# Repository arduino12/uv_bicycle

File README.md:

# UV Bicycle
This repository was created for a rotating laser array above circle colored with [photochromic](https://en.wikipedia.org/wiki/Photochromism) paint.
We were able to draw fading SMS messages on the circle from above by using the ultra violet lasers that activates the photochromatic dye for short periods of time.

The project was done for and in collaboration with the [Bloomfield Science Museum in Jerusalem](http://www.mada.org.il/en) that provided us with the hardware and photochromatic paint.
It was created to serve as a science exhibit that demonstrates the properties of photochromatic dyes.
The code is licensed with the MIT license so you are free to use the code for your own needs.

See the results: https://goo.gl/photos/oJwscTjsn2JnW7Ck9

## Repository Content
[/src/arduino_to_uv/](https://github.com/arduino12/uv_bicycle/tree/master/src/arduino_to_uv) - Arduino code for rotating led/laser array.

[/src/auto_cts/](https://github.com/arduino12/uv_bicycle/tree/master/src/auto_cts) - Arduino code for toggling CTS line to GSM module.

[/src/gsm_to_arduino/](https://github.com/arduino12/uv_bicycle/tree/master/src/gsm_to_arduino) - Pi main code for receiving logging and drawing the SMS messages. 

## Hardware
<img src="https://lh3.googleusercontent.com/Vc9EMIPHA8w_r2cUavsGSQO-o_p-7ncmXYEqYOy1NqUkL5eqGi37OpkXadukhLj22xZ-gRMF1kTlX_NGuJq8BMt3eHUF64rf8kQAkVgELNtqQZ1RMopb4X-rpCWFp0X3qmpbkKMwe0I_WGfFK4Y0_PC1MjWjIJ3T4Ibz2jPdR744nrNS3TW4o-I8bP2ekQa05fymQVjbHknS2VRSZ0DTwl79BUZwA_VtFqYXUJwPtxD64q70xKaM9rZHWuroJr_1Tvtd-X4EULkwvXKUlg1P7ToxBazeEolZ0sMSxTwca8a46mI9U5H4igfo2b5B4D7_b6VAIZAvufg7lnp_SHirEBCOUqLExb3ahMAZRm8fPo9suOPBamb8nU4uetgNMl8iYfZWosMtypwYz0UoY1q7np4bJ6RxMoacF1YhWF4UVPSs5c2owiwA5MacgWr0QcjLhOXokvbC5WcQ38CB4p-cbZNxGNrWULT_6ONU7YTXHPvQaKNxr3c_F1Vqt-jB5_UeZOAFuIAoNEPa4kCFHji4aErF4kzA6CDGKILxqji498P7u0TZostGEw3Fn8uNkkDoxx1JTORTo-OQx-Je5zLs8fBRl57VO6N1IjqmTV3mxX8bAGLKvdmcFl1H1_UraBbP3oRyOuiZWikjajVKhDTIFSlbFYo9egeu3pkob9Kr_HS7YDQ">
<img src="https://lh3.googleusercontent.com/Ws7JQw-yEKeiUe4MuJQAN-q8wx_f5K7RBDDxZ9f8wQQIW_8lA9Yw4n6IqJK_GnT0hbwdW7TLM-m-gelrgOvau5pxB6vvcL0IUWs8IOO5ovuf7cEzAAFZcjh-KP-J3fhh4H8FxVKoyaPNvuyuJGwxkWvGBafbCa8wj3TknDk1y6XuR6KxQ_zH66dlrq7bNpso4gAWbYyNidm6teT94X6_2um_1w_LaygNzx0y9oYFp9pRaNshwGENiCASdAd84XJyoEfFHm6JqLjo-RjeU93c4V7C7xSTb1NT4A-c7qdPuSsIp1EbnigUo7ll56vmy7caqoNtTOS2SGiKBetD4fq8ZSKgZ6Fa4dgx-YZiuOd23pawARR5CGtpw04KW2g3HyMuWi070UGC1EdrO68SzervdrS9uVxDwNguE_PY4yW4LJEckRW4u6W9sxowAWTuWKZvJDicob2_tlzZAGOmuAZKlW8aKlHq40BI1b61WPKIbscPgb4QIG1kB7d0ltgF0tWaYij5iwDBfQq8FyUTvc5_OfMTae2ZswM36q5LhByYsK_KRg5VsyydxD20RPjYVLZ8fsF3lGvVw8Zd_pon3TpEVTmDYJnUnama0IZVXObShmHL_anDgvr7-ycj7bS5GCZ7KQlDQ0UBXkGgK_qk0FnERgxz9sPKLAx6wxCItfvWbOjPZnQ">

### Pi Side
* Raspberry pi 3 with two USB-UART converters, provide both power and communication to BT and GSM modules.
* Extra arduino is needed because of AI-A6 GSM module bug that sends garbage in uart if CTS is not toggled.

### Bicycle Side
* The laser driver is ULN2003 - 7 NPN transistors in a single package.

## Software
* Must clone [infra](https://github.com/arduino12/infra) near this repo clone.
* For Google Sheets logger, put the json keys file near this repo.
* Better to auto run it with systemctl and see logs with journalctl on pi.

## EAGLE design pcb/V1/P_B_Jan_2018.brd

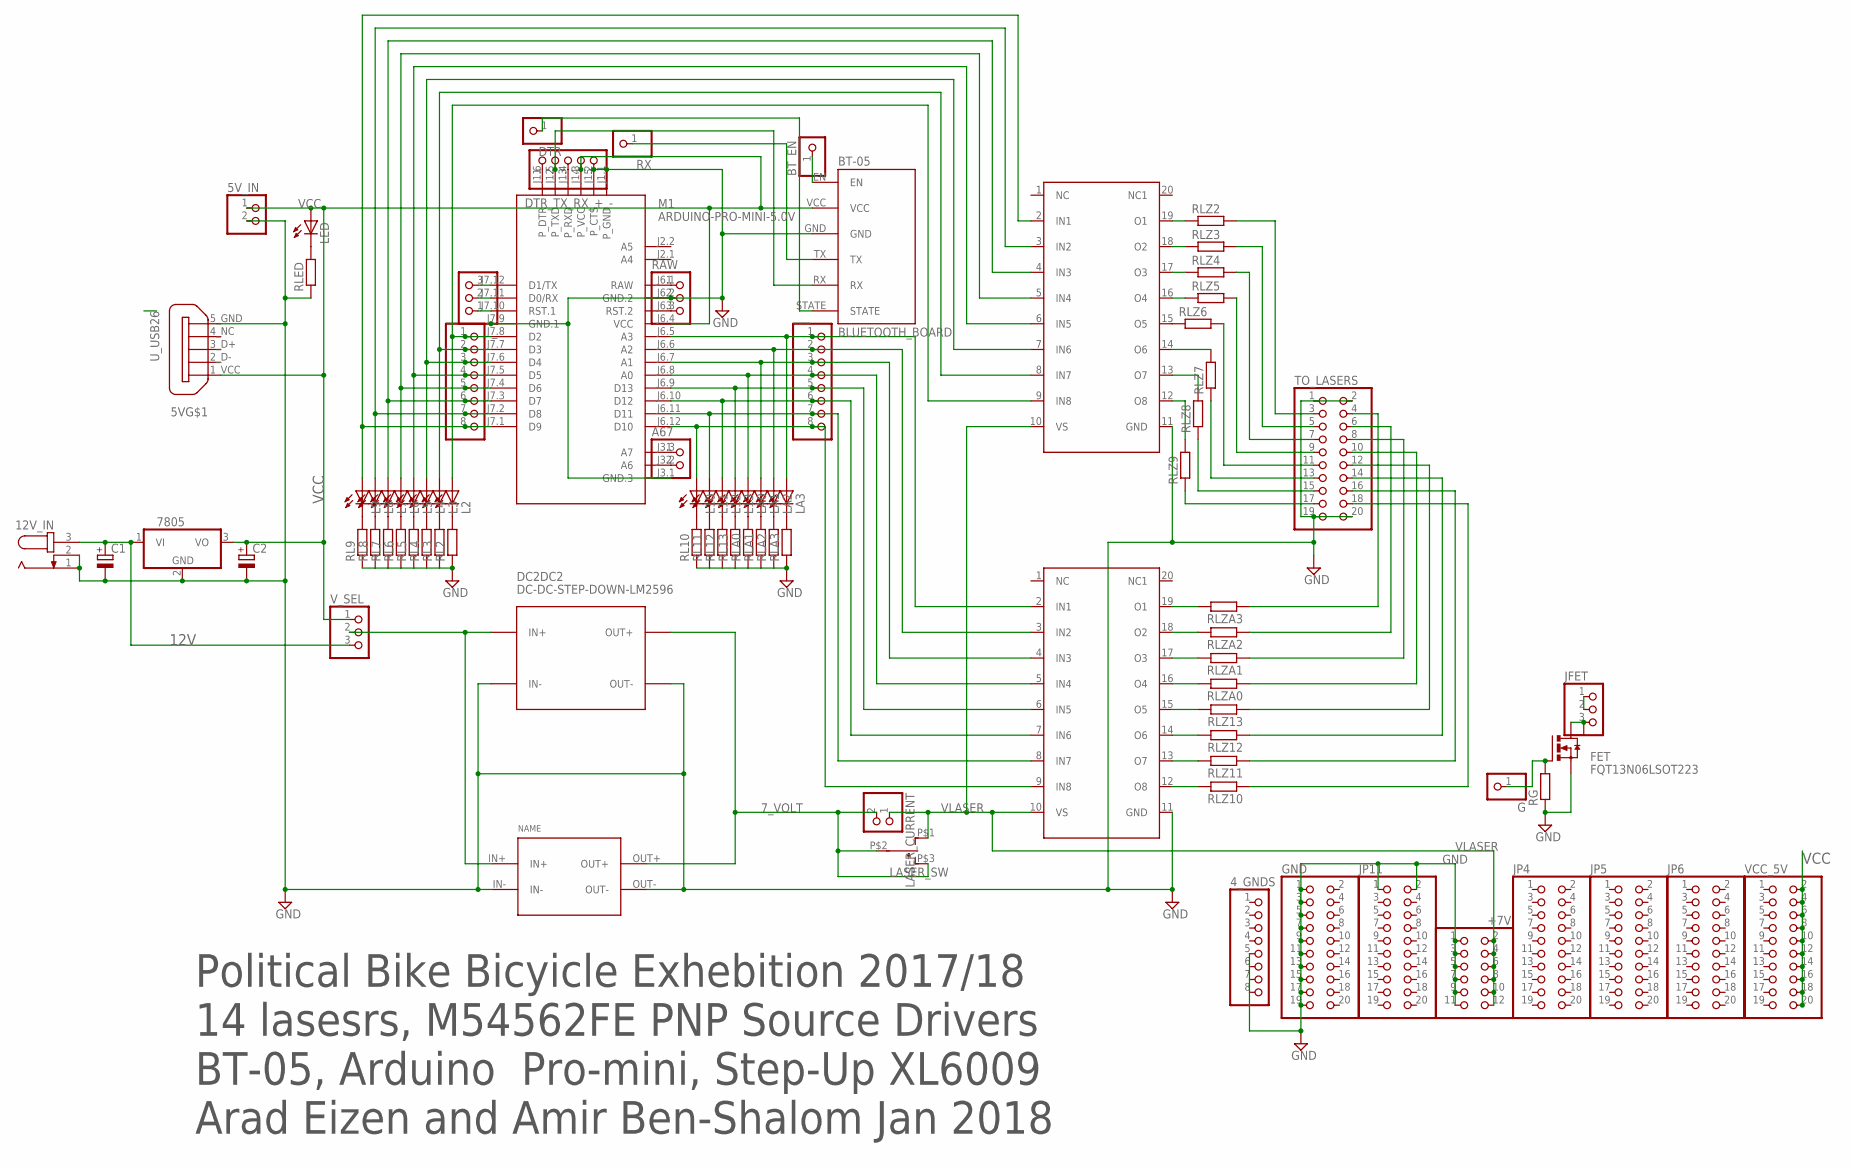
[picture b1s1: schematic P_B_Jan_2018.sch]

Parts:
4_GNDS: PINHD-1X8; 1X08
5V: U_USB26; U_USB_26
5V_IN: PINHD-1X2SQ&RND; 1X02_SQ&ROUND
12V_IN: JACK-PLUGHOLE_PAD; JACK_DC
7805: 7805TV; TO220V
+7V: PINHD-2X6; 2X06
A67: PINHD-1X2ROUND_PAD; 1X02_ROUND_PAD
BT-05: BLUETOOTH_BOARD; BT_BOARD_FOOTPRINT
BT_EN: PINHD-1X1; 1X01
C1: CPOL-EUE3.5-10; E3,5-10
C2: CPOL-EUE2.5-6; E2,5-6
DC2DC: DC2DC_CP8-ADJ; CP8-ADJ
DC2DC2: DC-DC-STEP-DOWN-LM2596
DTR: PINHD-1X1; 1X01
DTR_TX_RX_+_-: PINHD-1X5; 1X05
FET: FQT13N06LSOT223; SOT223
G: PINHD-1X1; 1X01
GND: PINHD-2X10; 2X10
JFET: PIN_HEAD_1X3_MARKED2.56; 1X3_MARKED
JP4, JP5, JP6, JP11: PINHD-2X10; 2X10
L2, L3, L4, L5, L6, L7, L8, L9, L10, L11, L12, L13: LEDCHIPLED_1206; CHIPLED_1206
LA0, LA1, LA2, LA3: LEDCHIPLED_1206; CHIPLED_1206
LASER_CURRENT: PINHD-1X2ROUND_PAD; 1X02_ROUND_PAD
LASER_SW: SW_SPDTSS_12D_00_W; SS_12D_00_W
LED: LED3MM
M1: ARDUINO-PRO-MINI-5.0V; ARDUINO-PRO-MINI
RAW: PINHD-1X3; 1X03
RG: R-EU_R0603; R0603
RL2, RL3, RL4, RL5, RL6, RL7, RL8, RL9, RL10, RL11, RL12, RL13: R-EU_R0603; R0603
RLA0, RLA1, RLA2, RLA3: R-EU_R0603; R0603
RLED: R-EU_R0603; R0603
RLZ2, RLZ3, RLZ4, RLZ5, RLZ6, RLZ7, RLZ8, RLZ9, RLZ10, RLZ11, RLZ12, RLZ13: R-EU_R0603; R0603
RLZA0, RLZA1, RLZA2, RLZA3: R-EU_R0603; R0603
RX: PINHD-1X1; 1X01
TO_LASERS: PINHD-2X10; 2X10
U$5, U$6: M54562P-SOP-20; P-SOP-20
VCC_5V: PINHD-2X10; 2X10
V_SEL: PIN_HEAD_1X3_MARKED2.56; 1X3_MARKED
_: PINHD-1X3; 1X03
__: PINHD-1X8; 1X08
___: PINHD-1X8; 1X08

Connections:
7_VOLT: DC2DC.OUT+, DC2DC2.OUT+, LASER_CURRENT.2, LASER_SW.P$2, LASER_SW.P$3 (S)
12V: 12V_IN.3, 7805.1 (VI), C1.+, V_SEL.3
A0: LA0.A, M1.J6.8 (A0), U$6.5 (IN4), ___.4
A1: LA1.A, M1.J6.7 (A1), U$6.4 (IN3), ___.3
A2: LA2.A, M1.J6.6 (A2), U$6.3 (IN2), ___.2
A3: LA3.A, M1.J6.5 (A3), U$6.2 (IN1), ___.1
D10: L10.A, M1.J6.12 (D10), U$6.9 (IN8), ___.8
D11: L11.A, M1.J6.11 (D11), U$6.8 (IN7), ___.7
D12: L12.A, M1.J6.10 (D12), U$6.7 (IN6), ___.6
D13: L13.A, M1.J6.9 (D13), U$6.6 (IN5), ___.5
GND: 4_GNDS.5, 4_GNDS.6, 4_GNDS.7, 4_GNDS.8, 5V.5_GND, 5V_IN.2, 12V_IN.1, 12V_IN.2, 7805.2 (GND), +7V.1, +7V.3, +7V.5, +7V.7, +7V.9, +7V.11, BT-05.GND, C1.-, C2.-, DC2DC.IN-, DC2DC.OUT-, DC2DC2.IN-, DC2DC2.OUT-, DTR_TX_RX_+_-.5, FET.3 (S), GND.1, GND.3, GND.5, GND.7, GND.9, GND.11, GND.13, GND.15, GND.17, GND.19, JP11.1, JP11.2, M1.J1.1 (P_GND), M1.J1.2 (P_CTS), M1.J3.1 (GND.3), M1.J6.2 (GND.2), M1.J7.9 (GND.1), RAW.2, RG.1, RL2.1, RL3.1, RL4.1, RL5.1, RL6.1, RL7.1, RL8.1, RL9.1, RL10.1, RL11.1, RL12.1, RL13.1, RLA0.1, RLA1.1, RLA2.1, RLA3.1, RLED.1, TO_LASERS.1, TO_LASERS.2, TO_LASERS.19, TO_LASERS.20, U$5.11 (GND), U$6.11 (GND)
unnamed: RLZ2.2, TO_LASERS.3
unnamed: RLZ3.2, TO_LASERS.5
unnamed: RLZ4.2, TO_LASERS.7
unnamed: RLZ5.2, TO_LASERS.9
unnamed: RLZ6.2, TO_LASERS.11
unnamed: RLZ7.1, TO_LASERS.13
unnamed: RLZ8.1, TO_LASERS.15
unnamed: RLZ9.1, TO_LASERS.17
unnamed: RLZA3.1, TO_LASERS.4
unnamed: RLZA2.1, TO_LASERS.6
unnamed: L3.A, M1.J7.7 (D3), U$5.8 (IN7), __.2
unnamed: L4.A, M1.J7.6 (D4), U$5.7 (IN6), __.3
unnamed: L5.A, M1.J7.5 (D5), U$5.6 (IN5), __.4
unnamed: L6.A, M1.J7.4 (D6), U$5.5 (IN4), __.5
unnamed: L7.A, M1.J7.3 (D7), U$5.4 (IN3), __.6
unnamed: L8.A, M1.J7.2 (D8), U$5.3 (IN2), __.7
unnamed: L9.A, M1.J7.1 (D9), U$5.2 (IN1), __.8
unnamed: L2.A, M1.J7.8 (D2), U$5.9 (IN8), __.1
unnamed: RLZA1.1, TO_LASERS.8
unnamed: RLZA0.1, TO_LASERS.10
unnamed: RLZ13.1, TO_LASERS.12
unnamed: RLZ12.1, TO_LASERS.14
unnamed: RLZ11.1, TO_LASERS.16
unnamed: RLZ10.1, TO_LASERS.18
unnamed: RLZ3.1, U$5.18 (O2)
unnamed: RLZ4.1, U$5.17 (O3)
unnamed: BT-05.STATE, DTR.1
unnamed: BT-05.RX, DTR_TX_RX_+_-.2, M1.J1.5 (P_TXD)
unnamed: BT-05.TX, RX.1
unnamed: RLZ2.1, U$5.19 (O1)
unnamed: RLZ5.1, U$5.16 (O4)
unnamed: RLZ6.1, U$5.15 (O5)
unnamed: RLZ7.2, U$5.14 (O6)
unnamed: RLZ8.2, U$5.13 (O7)
unnamed: RLZ9.2, U$5.12 (O8)
unnamed: RLZ10.2, U$6.12 (O8)
unnamed: RLZ11.2, U$6.13 (O7)
unnamed: RLZ12.2, U$6.14 (O6)
unnamed: RLZ13.2, U$6.15 (O5)
unnamed: RLZA0.2, U$6.16 (O4)
unnamed: RLZA1.2, U$6.17 (O3)
unnamed: RLZA2.2, U$6.18 (O2)
unnamed: RLZA3.2, U$6.19 (O1)
unnamed: L2.C, RL2.2
unnamed: L3.C, RL3.2
unnamed: L4.C, RL4.2
unnamed: L5.C, RL5.2
unnamed: L6.C, RL6.2
unnamed: L7.C, RL7.2
unnamed: L8.C, RL8.2
unnamed: L9.C, RL9.2
unnamed: LED.K (C), RLED.2
unnamed: M1.J7.10 (RST.1), _.1
unnamed: DC2DC.IN+, DC2DC2.IN+, V_SEL.2
unnamed: M1.J7.11 (D0/RX), _.2
unnamed: M1.J7.12 (D1/TX), _.3
unnamed: A67.1, M1.J3.3 (A7)
unnamed: A67.2, M1.J3.2 (A6)
unnamed: LA3.C, RLA3.2
unnamed: LA2.C, RLA2.2
unnamed: LA1.C, RLA1.2
unnamed: LA0.C, RLA0.2
unnamed: L13.C, RL13.2
unnamed: L12.C, RL12.2
unnamed: L11.C, RL11.2
unnamed: L10.C, RL10.2
unnamed: M1.J6.1 (RAW), RAW.1
unnamed: M1.J6.3 (RST.2), RAW.3
unnamed: FET.1 (G), G.1, RG.2
unnamed: JFET.1, JFET.2
unnamed: DTR_TX_RX_+_-.3, M1.J1.4 (P_RXD)
unnamed: DTR_TX_RX_+_-.1, M1.J1.6 (P_DTR)
unnamed: FET.2 (D), FET.4 (D1), JFET.3
unnamed: BT-05.EN, BT_EN.1
VCC: 5V.1_VCC (1_VDD), 5V_IN.1, 7805.3 (VO), BT-05.VCC, C2.+, DTR_TX_RX_+_-.4, LED.A, M1.J1.3 (P_VCC), M1.J6.4 (VCC), VCC_5V.2, VCC_5V.4, VCC_5V.6, VCC_5V.8, VCC_5V.10, VCC_5V.12, VCC_5V.14, VCC_5V.16, VCC_5V.18, VCC_5V.20, V_SEL.1
VLASER: +7V.2, +7V.4, +7V.6, +7V.8, +7V.10, +7V.12, LASER_CURRENT.1, LASER_SW.P$1 (O), U$5.10 (VS), U$6.10 (VS)

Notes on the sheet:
Political Bike Bicyicle Exhebition 2017/18 14 lasesrs, M54562FE PNP Source Drivers BT-05, Arduino Pro-mini, Step-Up XL6009 Arad Eizen and Amir Ben-Shalom Jan 2018

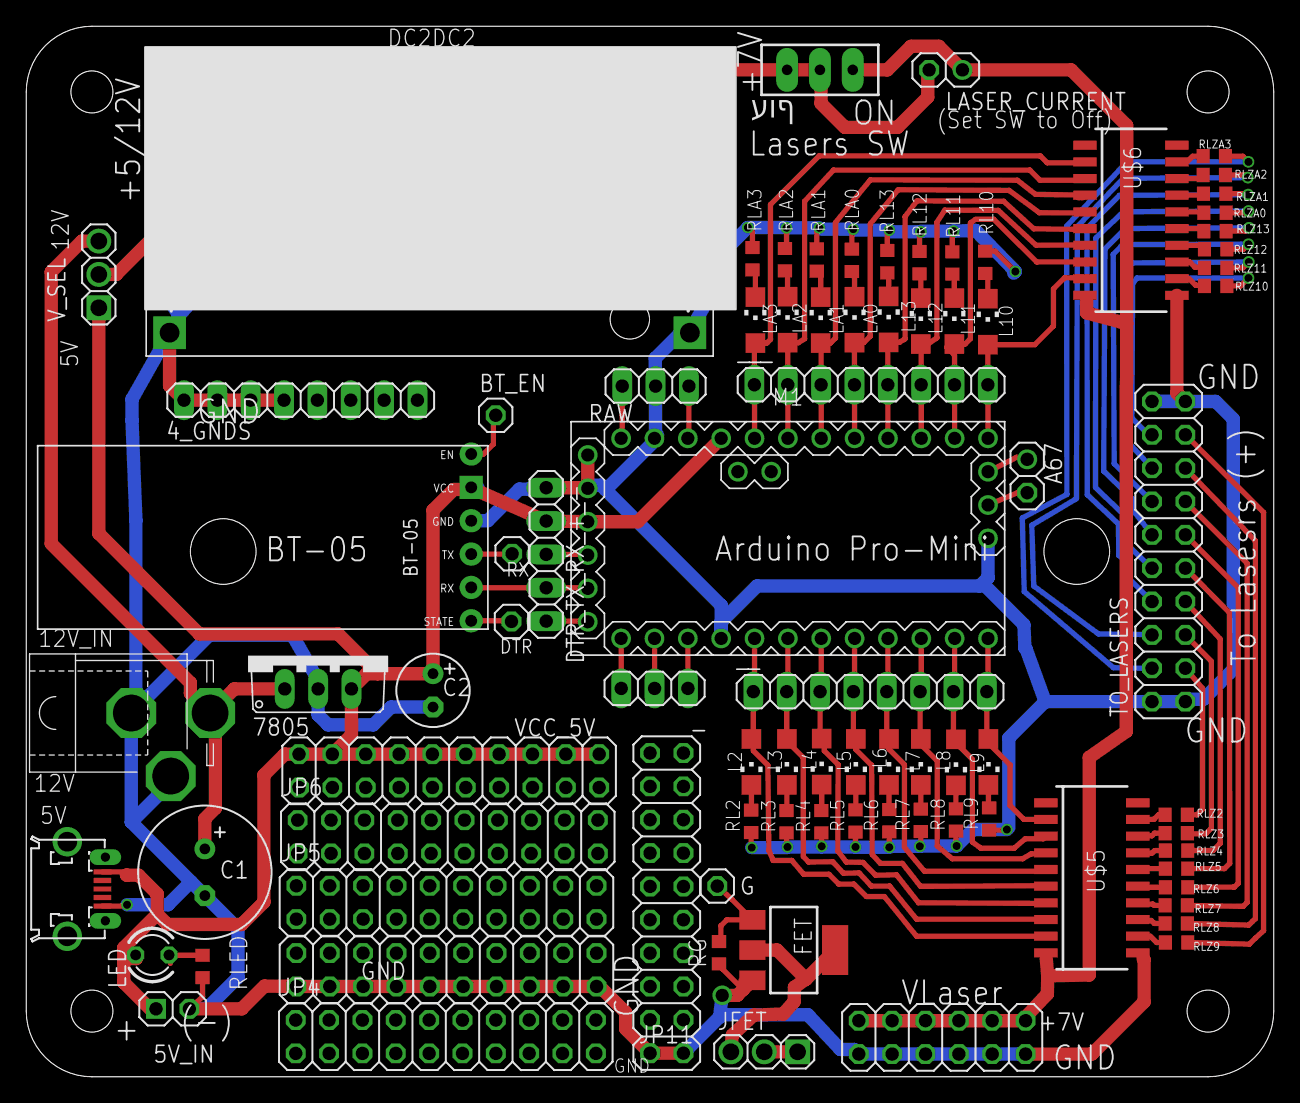
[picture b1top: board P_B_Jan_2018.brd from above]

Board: 2 copper layers, 95.0 x 80.0 mm, 87 parts (0 on the bottom side), 87 nets.

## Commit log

2017-07-03 :confetti_ball: Added .gitattributes & .gitignore files
2017-07-03 add uv_bicycle docs and src!
2017-07-04 add logor
2017-07-05 rename so IDE will be happy
2017-07-05 fix to use FETs
2017-07-05 improve doc
2017-07-08 add logger
2017-07-09 fix arduino code
2017-07-17 add rotating logger
2017-08-16 add sheets sms logger
2017-08-18 add file sms logger
2017-08-19 add comments and marge port constants
2017-08-19 add snippets.sh
2017-08-20 fix httplib2 cache bug in windows
2017-08-20 remove images
2017-08-22 fix utf8 bug, and limit message size to 40 unicode chars
2017-08-22 add fix texts
2017-08-23 add documentation to all functions and definitions
2017-08-23 add readme.md
2017-09-23 add pi snippets
2017-10-05 add sms command for testing using email address
2017-10-13 add M590 gsm module
2017-10-13 m590 event name change
2017-10-13 fix 2
2017-10-13 final m590 fix!
2017-11-23 replace M590 with SIM800
2017-11-23 Move from 7 to 14 lasers, add german font
2017-12-15 move to sim800 gsm module
2017-12-21 fix email to picture logic
2018-04-15 change arduino code pin mapping and more
2018-04-15 add pcb
2018-04-21 fix for v2
2020-10-15 add unicode support
